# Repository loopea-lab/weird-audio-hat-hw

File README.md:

# Weird Audio HAT R1.1

A WM8960 sound card for the Raspberry Pi: stereo line in and out, headphone amp, mono out and
a microphone input with bias. It shows up as a normal ALSA sound card.

## Specifications

| | |
|---|---|
| Codec | WM8960, stereo, 24-bit |
| Sample rates | 44.1 kHz family (master clock 11.2896 MHz) |
| Sample formats | `S16_LE`, `S24_LE`, `S32_LE` |
| Control | I2C, address `0x1A` |
| Frequency response | ±0.5 dB, 100 Hz – 8 kHz † |
| Output THD (DAC) | 0.003 % at 1 kHz † |
| Crosstalk between inputs | −67 to −92 dB across the band † |
| MICBIAS | ~3 V (0.9 × AVDD) † |
| Inputs | single-ended, line level |
| Outputs | stereo line / headphone, mono |

† measured on fabricated boards.

## Requirements

**Raspberry Pi Zero 2W on 32-bit Raspberry Pi OS** (tested). Pi 1, Zero, 2 and 3 on a 32-bit OS
should work but are untested. **Not supported:** Pi 4, Pi 5, or any 64-bit OS — the codec has no
oscillator, and the helper that clocks it from the Pi's GPCLK0 only knows the 32-bit register
addresses of the older chips.

48 kHz needs a different clock and a device-tree change.

## Connectors

Names as printed on the board. The schematic designator is in the last column.

| On the board | Type | Carries | Schematic |
|---|---|---|---|
| **IN L** | 3.5 mm jack | Line in L (tip) | J5 |
| **IN R** | 3.5 mm jack | Line in R (tip), or an electret mic with **MIC-R BIAS** on | J1 |
| **OUT L/R** | 3.5 mm stereo jack | Line / headphone out — tip L, ring R \* | J4 |
| **OUT MONO** | 3.5 mm jack | Mono out (tip) — the sum of L and R | J2 |
| **MIC-R BIAS** | slide switch | Puts MICBIAS on **IN R** | SW1 |
| 4-pin header, left edge | 1×4 header | Line in from a panel — 1 GND · 2 R · 3 GND · 4 L | J6 |
| 4-pin header, right edge | 1×4 header | Line out to a panel — 1 GND · 2 R · 3 GND · 4 L | J7 |
| 40-pin header | 2×20 Pi header | I2C (3, 5) · I2S (12, 35, 38, 40) · GPCLK0 (7) · 3.3 V / 5 V. Free GPIOs (BCM): 5–17 and 22–27, including SPI0 and the UART; 0 and 1 are left for a HAT ID EEPROM | J3 |

Left and right edges as seen from the top, with the jacks facing you.

\* R1.1: L and R are swapped; the driver's `DAC L/R Swap` control corrects it.

## Using it

Install the driver: [weird-audio-hat-driver](https://github.com/loopea-lab/weird-audio-hat-driver).
It covers recording, playback, routing and gain.

- **Inputs are single-ended** (LINPUT3 / RINPUT3). The codec's differential mode is not wired.
- **Headphone out** is AC-coupled; it drives 32 Ω headphones or a line input.
- **IN R is line or microphone, chosen by the MIC-R BIAS switch:** off = line input; on = electret
  mic input, biased at ~3 V through 1 kΩ. The driver keeps `MIC Bias` on, so the switch is the only
  thing to set. Don't plug a line source into IN R with the switch on: it loads the source and puts
  3 V DC on it.

## Troubleshooting

**No sound card in `aplay -l`.** Not on a Pi 5? Driver installed? Do not add
`dtoverlay=wm8960-soundcard` to `config.txt` — the driver's service loads it. `i2cdetect -y 1`
should show `1a`.

**Recording fails or is silent.** Use `S32_LE` (or `S16_LE` / `S24_LE`); `S24_3LE` fails and
looks like dead hardware. If the format is right, the input path is muted — see the driver README.

## Combine it with

- [Weird Piano HAT](https://github.com/loopea-lab/weird-piano-hat) — keys and pots, an
  instrument with Pure Data.
- [Weird MCP Inputs](https://github.com/loopea-lab/weird-mcp-inputs) + Control Board + panel —
  a Eurorack module. The two 4-pin headers carry audio to the panel; the stacking header passes the MCP's
  signals through, so use a good one.

## License

CC BY-SA 4.0 — see [`LICENSE`](LICENSE). Datasheets in `datasheets/` are copyright of their manufacturers.

Copyright © 2024–2026 Weird Electronics / Loopea Lab.

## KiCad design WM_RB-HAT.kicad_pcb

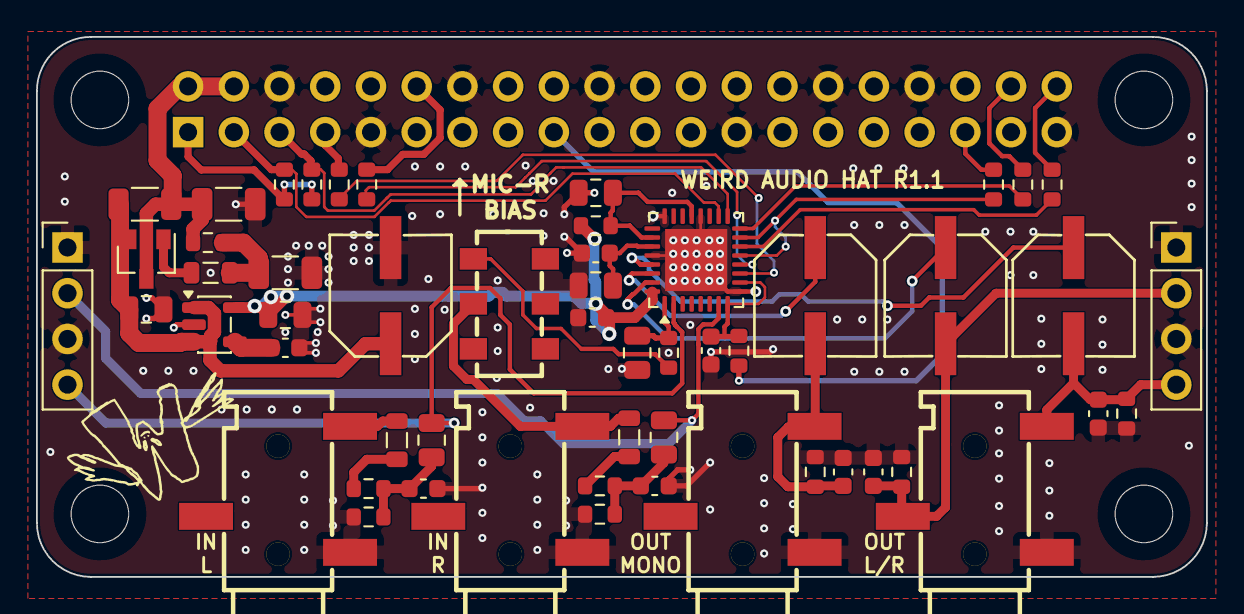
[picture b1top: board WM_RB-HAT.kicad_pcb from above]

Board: 4 copper layers, 65.0 x 30.0 mm, 59 parts (1 on the bottom side), 40 nets.

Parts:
C2, C8, C31, C32: 4.7u; C_0805_2012Metric
C3, C5: 100n; C_0603_1608Metric
C7, C9, C20, C21, C29, C30: 390p; C_0603_1608Metric
C12: 22n; C_0603_1608Metric
C18, C19: 1uF X7R; C_0805_2012Metric
C22, C35: 10-47u 1206 >10V; C_1206_3216Metric
C36: 4.7uF X7R; C_0805_2012Metric
CP1, CP2, CP3, CP4: 220uF 16V; CAP-SMD_BD6.3-L6.6-W6.6-FD
FB1, FB2, FB3: 220-1k; L_0805_2012Metric
H1, H2, H5, H6: 3mm_Mounting_Hole; MountingHole_3.2mm_M3_Keepout
J1, J2, J4, J5: AudioJack3; AUDIO-SMD_PJ-320B
J3: 2x20 Pins; PinSocket_2x20_P2.54mm_Vertical
J6: Audio In; PinHeader_1x04_P2.54mm_Vertical
J7: Audio Out; PinHeader_1x04_P2.54mm_Vertical
Q1: BC817; SOT-23_Mefores_Pads
R2, R3, R4, R5, R26: 270; R_0603_1608Metric
R6, R22, R23: 0R; R_0603_1608Metric
R7, R8: 100K; R_0603_1608Metric
R9, R10, R24: 100R; R_0603_1608Metric
R11: 10 1206; R_1206_3216Metric
R12, R15: 1K; R_0603_1608Metric
R13, R14: 4.7K; R_0603_1608Metric
R27: 0; R_0603_1608Metric
SW1: SSSS213202; SW-TH_SSSS213202
U1: WM8960; QFN-32-1EP_5x5mm_P0.5mm_EP3.45x3.45mm
U4: MCP1711T-33 /OT; TSOT-23-5

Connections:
+3.3V: J3.17 (P3V3), R27.2
+3.3VA: C5.1, C31.1, R24.1, U1.32 (AVDD), U4.5 (VOUT)
+5V: C35.1, J3.2 (P5V), J3.4 (P5V), Q1.3 (C), R11.2, R12.2
+VREGIN: C32.1, CP3.1, Q1.2 (E), R11.1, U4.1 (VIN), U4.3 (EN)
/CLK: R26.2, U1.11 (MCLK)
/HP_L: CP2.1, U1.29 (HP_R)
/HP_L_AC: C29.2, CP2.2, J4.T, J7.4, R22.2
/HP_R: CP1.1, U1.31 (HP_L)
/HP_R_AC: C30.2, CP1.2, J4.R, J7.2, R23.2
/I2C_SCL: J3.5 (BCM3/SCL), R13.1, U1.17 (SCLK)
/I2C_SDA: J3.3 (BCM2/SDA), R14.1, U1.18 (SDIN)
/I2S_ADC: J3.38 (I2S_ADC/BCM20), R5.2
/I2S_CLK: J3.12 (I2S_CLK/BCM18), R2.2
/I2S_DAC: J3.40 (I2S_DAC/BCM21), R3.2
/I2S_LRCLK: J3.35 (BCM19/I2S_LR), R4.2
/INPUT_L: FB2.1, J5.T
/INPUT_R: FB1.1, J1.T, SW1.2
/LINE_INPUT_L: C19.2, J6.4, U1.2 (LINPUT3/JD2)
/LINE_INPUT_R: C18.2, J6.2, U1.7 (RINPUT3/JD3)
/MICBIAS: C2.1, R15.2, U1.1 (MICBIAS)
/OUT_MONO: CP4.1, U1.30 (OUT3)
/OUT_MONO_AC: C9.2, CP4.2, J2.T, R6.2
/P3V3_HAT: J3.1 (P3V3), R13.2, R14.2
GND: C2.2, C3.2, C5.2, C7.1, C8.2, C9.1, C12.2, C20.1, C21.1, C22.2, C29.1, C30.1, C31.2, C32.2, C35.2, C36.2, CP3.2, J1.S, J2.S, J3.6 (GND), J3.9 (GND), J3.14 (GND), J3.20 (GND), J3.25 (GND), J3.30 (GND), J3.34 (GND), J3.39 (GND), J4.S, J5.S, J6.1, J6.3, J7.1, J7.3, R6.1, R7.1, R8.1, R22.1, R23.1, U1.9 (DGND), U1.20 (SPKGND2), U1.24 (SPKGND1), U1.28 (AGND), U1.33 (GND), U4.2 (GND)
unnamed: C18.1, C21.2, R8.2, R9.1
unnamed: C19.1, C20.2, R7.2, R10.1
unnamed: C22.1, FB3.1, R12.1
unnamed: FB1.2, R9.2
unnamed: FB2.2, R10.2
unnamed: J3.7 (BCM4/GPCLK0), R26.1
unnamed: FB3.2, Q1.1 (B)
unnamed: R15.1, SW1.3
unnamed: R5.1, U1.16 (ADCDAT)
unnamed: R4.1, U1.13 (DACRLC), U1.15 (ADCLRC/GPIO1)
unnamed: R2.1, U1.12 (BCLK)
unnamed: R3.1, U1.14 (DACAT)
unnamed: C3.1, R27.1, U1.8 (DCVDD), U1.10 (DBVDD)
unnamed: C8.1, R24.2, U1.21 (SPKVDD2), U1.26 (SPKVDD1)
unnamed: C7.2, C36.1, U1.27 (VMID)
unnamed: C12.1, U4.4 (SENSE/ADJ)

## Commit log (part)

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2024-04-04 Initial commit: Open-sourcing the hardware design of the Weird Audio Hat
2024-04-20 Added some notes for the next revision. General cleanup.
2024-10-10 Added PDF schematic
2025-09-25 Add assembly PDF and DRC updates for v1.0
2025-09-25 Add .gitignore for KiCad backup and temporary files
2025-10-29 Update KiCad project files to latest format version
    - Upgraded project file format from v1 to v3
    - Added new DRC rules: creepage, footprint_filters_mismatch, hole_to_hole, text_on_edge_cuts, track_angle, track_segment_length
    - Updated teardrop configuration format
    - Upgraded layer presets file from v3 to v5
    - Added net inspector panel configuration
    These changes were automatically applied by opening the project in a newer version of KiCad.
2025-10-29 Clean up v1.0 generated outputs and update .gitignore
    - Remove generated PDFs (assembly, schematic)
    - Remove BOM and plot files
    - Remove KiCad cache files
    - Update .gitignore to exclude: plots/, bom/, *.pdf, fp-info-cache
    - Include KiCad auto-formatting updates to PCB and schematic files
    Preparing development branch for v2 work.
2025-10-29 Add releases/ folder structure for manufacturing outputs
    - Created releases/ directory structure with v1.0 subdirectories
    - Added subdirectories: gerbers, assembly, schematic, bom
    - Updated .gitignore to track files in releases/ folder
    - Added README with release output guidelines
    This allows tracking of manufacturing outputs per version while
    keeping working directory outputs ignored.
2026-01-12 WIP v1.1: SMD migration + input simplification
    - Remove differential input stage, simplify jacks
    - Migrate to 0603, remove HandSolder footprints
    - Add LCSC codes, 4-layer stackup config
    - Add SMD libs and design docs
2026-01-12 Update PCB from schematic
2026-01-13 Fix ferrite bead LCSC code: C1029 → C85835
    C1029 was a 3.3nH inductor (0603), not a ferrite bead.
    C85835 is Murata BLM21AG102SN1D:
    - 1kΩ @ 100MHz
    - 0805 (matches footprint)
    - 600mA rated
    - Basic JLCPCB part
2026-01-13 Add missing LCSC codes for JLCPCB assembly
    Components added:
    - C2 (4.7u 0805): C1779
    - C5 (100n 0805): C49678
    - C7,C21,C29 (390p 0805): C1671
    - C22 (47u 1206): C96123
    - J1,J2,J4,J5 (PJ-320B): C18594
2026-02-06 WIP: PCB and schematic progress
2026-02-06 Add README with project documentation
    Covers WM8960 codec specs, layer stack, component BOM with LCSC codes,
    power architecture, audio specs, interfaces, and known v1.0 issues.
2026-03-02 WIP: 4-layer SIG/GND/GND/SIG stackup + SMD migration progress
2026-03-10 Rename audio I/O labels (LINE_INPUT, HP_AC)
2026-03-10 Resize PCB to Raspberry Pi Zero footprint
2026-03-11 PCB layout adjustments
2026-03-13 Add SSSS213202 slide switch library, PCB and schematic updates
    - Add Alps SSSS213202 SPDT switch: symbol, footprint, 3D model (LCSC C115375)
    - Register switch libraries in sym-lib-table and fp-lib-table
    - Schematic and PCB layout updates
2026-03-14 Add changelog 2026-03-13
2026-03-16 PCB routing progress, fix C36 VMID cap to 4.7uF X7R
2026-03-24 Zone clearance 0.3→0.2mm, add silkscreen SVGs
2026-03-24 Add revision R0.2, update title
2026-03-24 Add *.rpt to gitignore
2026-03-26 R1.1: HP output filter 100k→0Ω, silk labels OUT L/R, MIC-R BIAS
2026-06-24 Migrate project to KiCad 10 format
2026-06-24 Set R6/R22/R23 to 100K (fix output short, restore original bleed)
